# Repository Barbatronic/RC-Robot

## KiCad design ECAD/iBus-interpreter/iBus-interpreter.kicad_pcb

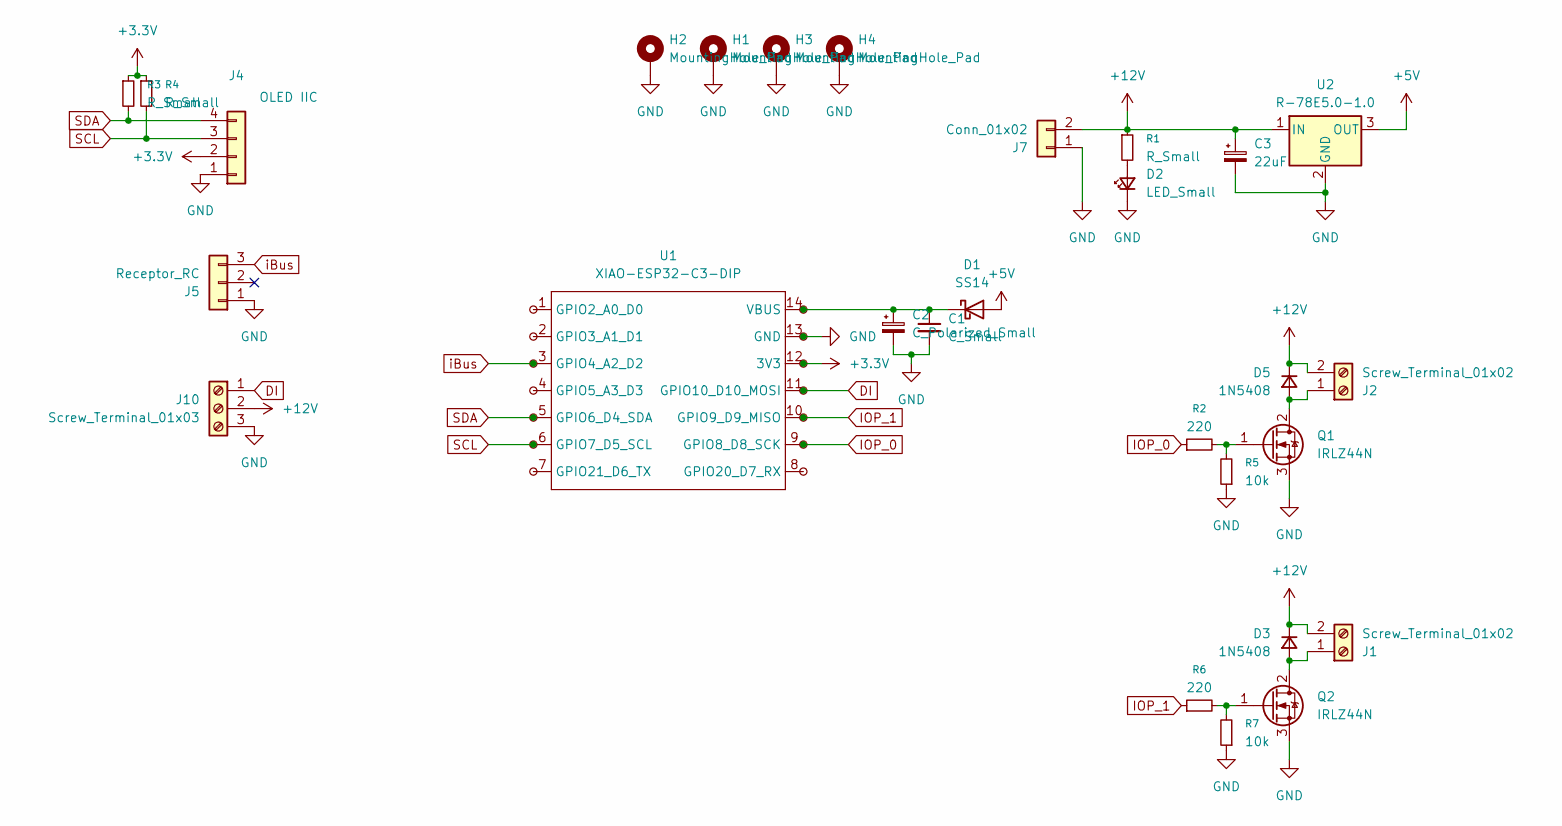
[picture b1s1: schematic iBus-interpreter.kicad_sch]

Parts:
C1: C_Small; C_1206_3216Metric_Pad1.33x1.80mm_HandSolder
C2: C_Polarized_Small; CP_Elec_5x5.4
C3: 22uF; CP_Elec_5x5.4
D1: SS14; D_SMA_Handsoldering
D2: LED_Small; LED_1206_3216Metric_Pad1.42x1.75mm_HandSolder
D3, D5: 1N5408; D_DO-201AD_P5.08mm_Vertical_AnodeUp
H1, H2, H3, H4: MountingHole_Pad; MountingHole_3.2mm_M3_Pad_Via
J1, J2: Screw_Terminal_01x02; TerminalBlock_Phoenix_MKDS-1,5-2_1x02_P5.00mm_Horizontal
J4: OLED IIC; PinHeader_1x04_P2.54mm_Vertical
J5: Receptor_RC; PinHeader_1x03_P2.54mm_Vertical
J7: Conn_01x02; AMASS_XT60-M_1x02_P7.20mm_Vertical
J10: Screw_Terminal_01x03; TerminalBlock_Phoenix_MKDS-1,5-3_1x03_P5.00mm_Horizontal
Q1, Q2: IRLZ44N; TO-220-3_Vertical
R1, R3, R4: R_Small; R_1206_3216Metric_Pad1.30x1.75mm_HandSolder
R2, R6: 220; R_1206_3216Metric_Pad1.30x1.75mm_HandSolder
R5, R7: 10k; R_1206_3216Metric_Pad1.30x1.75mm_HandSolder
TP1, TP2, TP3, TP4, TP5, TP6, TP7, TP8, TP9, TP10, TP11, TP12, TP13, TP14: PinHeader_1x01_P2.54mm_Vertical
U1: XIAO-ESP32-C3-DIP
U2: R-78E5.0-1.0; Converter_DCDC_RECOM_R-78E-0.5_THT

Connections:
+3.3V: J4.2, R3.1, R4.1, TP1.1, U1.12 (3V3)
+5V: D1.2 (A), U2.3 (OUT)
+12V: C3.1, D3.1 (K), D5.1 (K), J1.2, J2.2, J7.2, J10.2, R1.1, U2.1 (IN)
DI: J10.1, TP12.1, U1.11 (GPIO10_D10_MOSI)
GND: C1.2, C2.2, C3.2, D2.1 (K), H1.1, H2.1, H3.1, H4.1, J4.1, J5.1, J7.1, J10.3, Q1.3 (S), Q2.3 (S), R5.1, R7.1, TP13.1, U1.13 (GND), U2.2 (GND)
IOP_0: R2.1, TP10.1, U1.9 (GPIO8_D8_SCK)
IOP_1: R6.1, TP11.1, U1.10 (GPIO9_D9_MISO)
unnamed: C1.1, C2.1, D1.1 (K), TP14.1, U1.14 (VBUS)
unnamed: D2.2 (A), R1.2
unnamed: D3.2 (A), J1.1, Q2.2 (D)
unnamed: D5.2 (A), J2.1, Q1.2 (D)
unnamed: Q1.1 (G), R2.2, R5.2
unnamed: Q2.1 (G), R6.2, R7.2
unnamed: TP3.1, U1.1 (GPIO2_A0_D0)
unnamed: TP2.1, U1.2 (GPIO3_A1_D1)
unnamed: TP5.1, U1.4 (GPIO5_A3_D3)
unnamed: TP9.1, U1.8 (GPIO20_D7_RX)
unnamed: TP8.1, U1.7 (GPIO21_D6_TX)
SCL: J4.3, R4.2, TP7.1, U1.6 (GPIO7_D5_SCL)
SDA: J4.4, R3.2, TP6.1, U1.5 (GPIO6_D4_SDA)
iBus: J5.3, TP4.1, U1.3 (GPIO4_A2_D2)

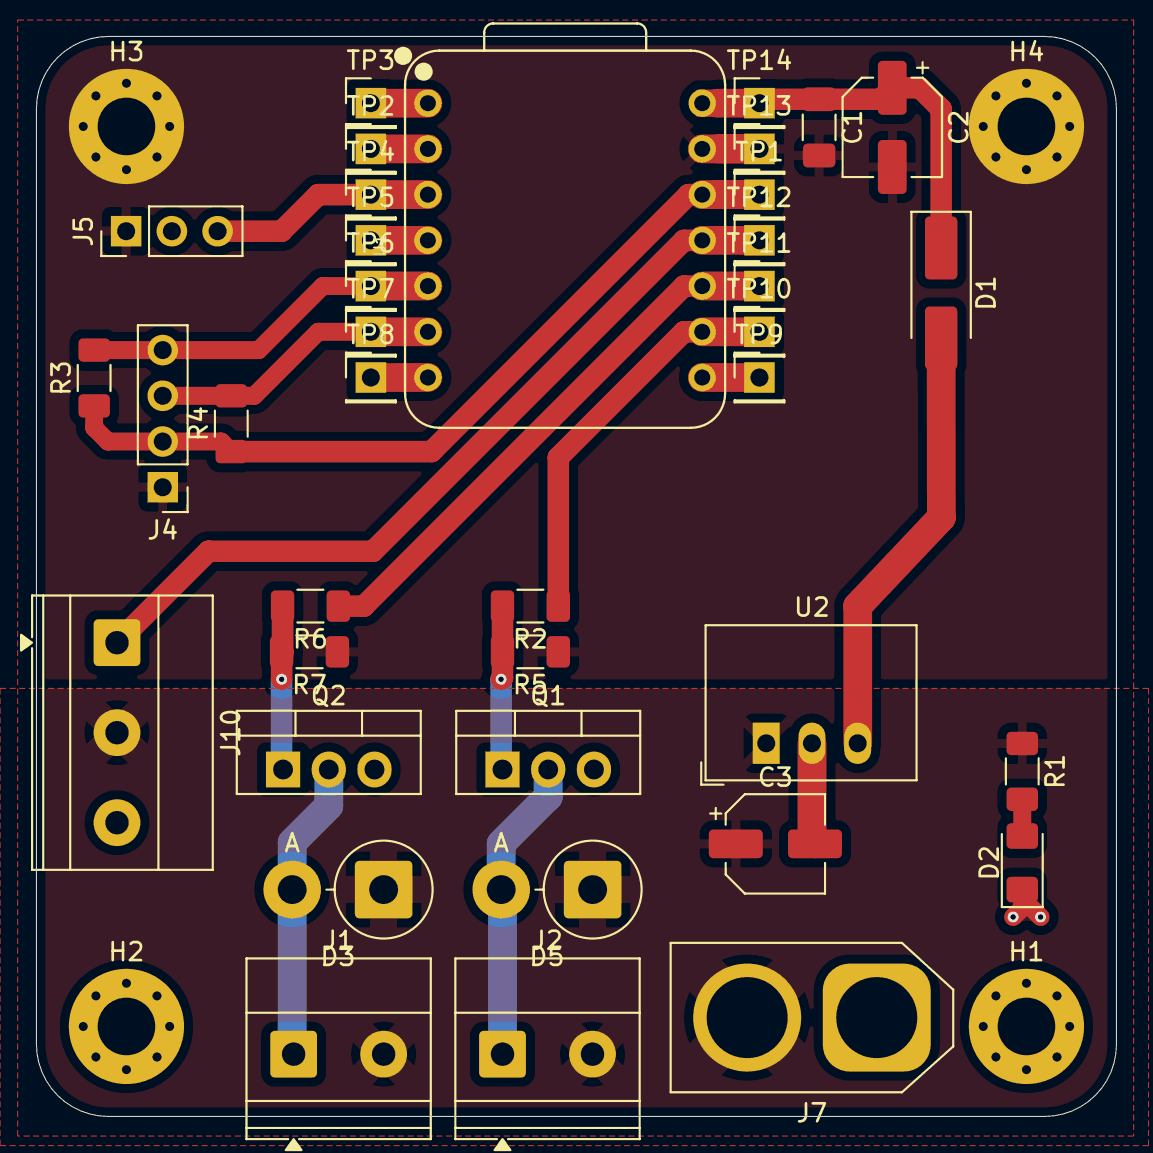
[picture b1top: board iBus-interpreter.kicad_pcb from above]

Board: 2 copper layers, 60.0 x 60.0 mm, 42 parts (0 on the bottom side), 21 nets.

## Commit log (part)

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2025-08-24 first commit - old project
2025-08-30 live 235
2025-08-31 adjust core wheel
2025-08-31 2020 profil visual update
2025-08-31 visual
2025-09-06 new axle for linear actuator
2025-09-12 electronic plate
2025-12-22 Update RC-Robot FreeCAD project files
2026-02-28 Clean
2026-02-28 adapt to FC 1.2dev
2026-03-01 New assembly V1.2dev
2026-03-01 Color change
2026-03-01 adapt infill - add all lateral carters
2026-03-01 new top carter
2026-03-01 add rear carter - modify lateral carter
2026-03-02 add cable connection and screw connection
2026-03-02 New support plate for battery
2026-03-02 update data infos
2026-03-08 Testing iBus
2026-03-10 update for WS2815
2026-03-10 Add clip and led pannel
2026-03-12 top battery
2026-04-08 carter and internal supports
2026-04-12 New PCB
2026-04-12 fab files
